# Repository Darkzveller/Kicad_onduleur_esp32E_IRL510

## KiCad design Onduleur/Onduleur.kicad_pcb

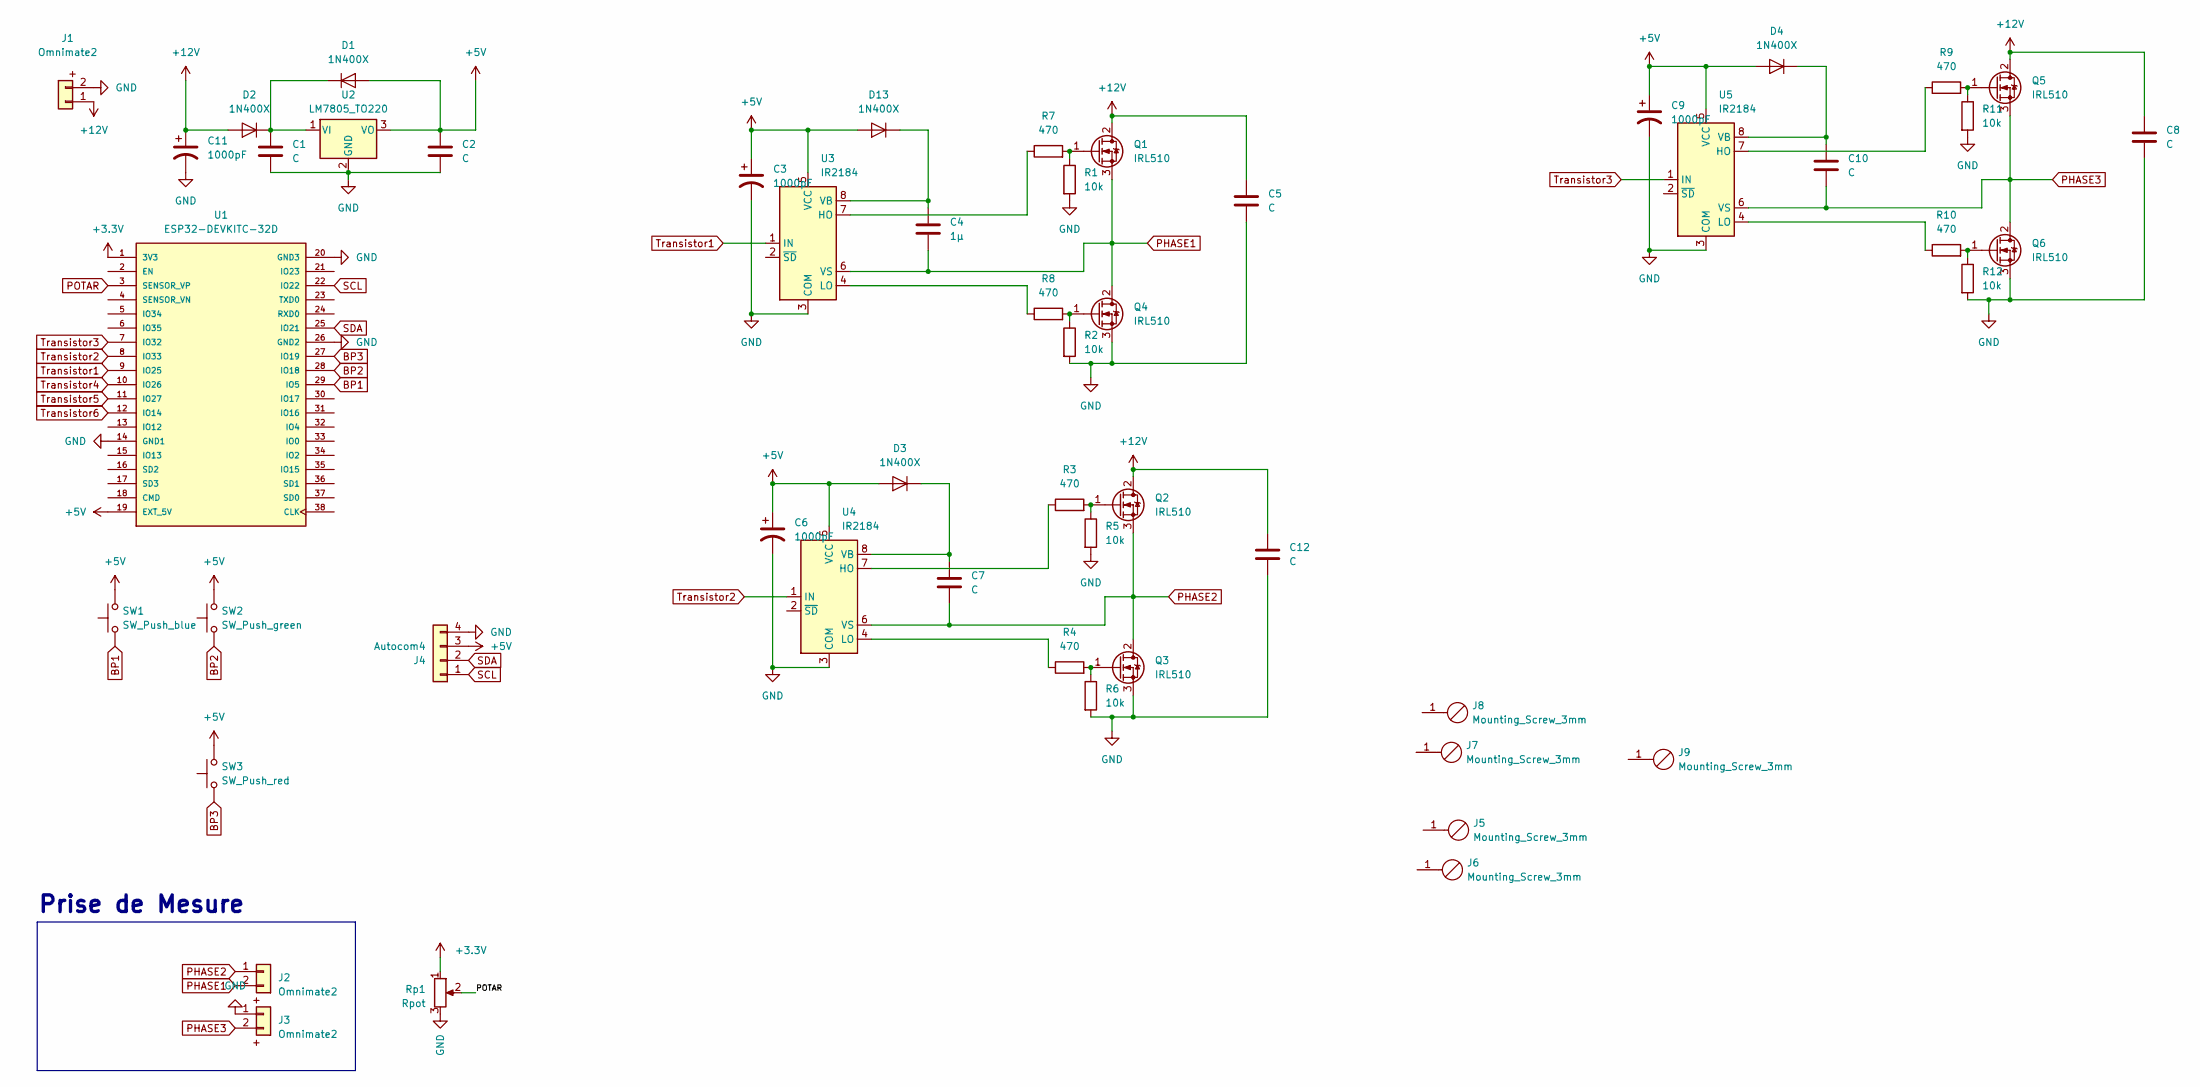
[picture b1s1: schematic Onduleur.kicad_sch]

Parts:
C1, C2, C7, C10: C; C_Rect_L7.0mm_W2.5mm_P5.00mm
C3, C6, C9: 1000pF; CP_Radial_D5.0mm_P2.50mm
C4: 1µ; C_Rect_L7.0mm_W2.5mm_P5.00mm
C5, C8, C12: C; C_Rect_L19.0mm_W5.0mm_P15.00mm
C11: 1000pF; CP_Radial_D10.0mm_P5.00mm
D1, D2, D3, D4, D13: 1N400X; D_DO-41_SOD81_P10.16mm_Horizontal
J1, J2, J3: Omnimate2; OmnimateSL-5,08_1x02_P5.08mm_Vertical
J4: Autocom4; PinHeader_1x04_P2.00mm_Vertical
J5, J6, J7, J8, J9: Mounting_Screw_3mm
Q1, Q2, Q3, Q4, Q5, Q6: IRL510; TO-220-3_Horizontal_TabDown
R1, R2, R5, R6, R11, R12: 10k; R_Axial_DIN0207_L6.3mm_D2.5mm_P10.16mm_Horizontal
R3, R4, R7, R8, R9, R10: 470; R_Axial_DIN0207_L6.3mm_D2.5mm_P10.16mm_Horizontal
Rp1: Rpot; Potentiometer_ACP_CA9-H5_Horizontal
SW1: SW_Push_blue; SW_PUSH_5mm_blue
SW2: SW_Push_green; SW_PUSH_5mm_green
SW3: SW_Push_red; SW_PUSH_5mm_red
U1: ESP32-DEVKITC-32D; MODULE_ESP32-DEVKITC-32D; PARTREV 4
U2: LM7805_TO220; TO-220-3_Horizontal_TabDown
U3, U4, U5: IR2184; DIP-8_W7.62mm_LongPads

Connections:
+3.3V: Rp1.1, U1.1 (3V3)
+5V: C2.1, C3.1, C6.1, C9.1, D1.2 (A), D3.2 (A), D4.2 (A), D13.2 (A), J4.3, SW1.2, SW2.2, SW3.2, U1.19 (EXT_5V), U2.3 (VO), U3.5 (VCC), U4.5 (VCC), U5.5 (VCC)
+12V: C5.1, C8.1, C11.1, C12.1, D2.2 (A), J1.1, Q1.2 (D), Q2.2 (D), Q5.2 (D)
BP1: SW1.1, U1.29 (IO5)
BP2: SW2.1, U1.28 (IO18)
BP3: SW3.1, U1.27 (IO19)
GND: C1.2, C2.2, C3.2, C5.2, C6.2, C8.2, C9.2, C11.2, C12.2, J1.2, J3.1, J4.4, Q3.3 (S), Q4.3 (S), Q6.3 (S), R1.2, R2.2, R5.2, R6.2, R11.2, R12.2, Rp1.3, U1.14 (GND1), U1.20 (GND3), U1.26 (GND2), U2.2 (GND), U3.3 (COM), U4.3 (COM), U5.3 (COM)
unnamed: C1.1, D1.1 (K), D2.1 (K), U2.1 (VI)
unnamed: C7.1, D3.1 (K), U4.8 (VB)
unnamed: C10.1, D4.1 (K), U5.8 (VB)
unnamed: C4.1, D13.1 (K), U3.8 (VB)
unnamed: Q1.1 (G), R1.1, R7.2
unnamed: Q2.1 (G), R3.2, R5.1
unnamed: Q3.1 (G), R4.2, R6.1
unnamed: Q4.1 (G), R2.1, R8.2
unnamed: Q5.1 (G), R9.2, R11.1
unnamed: Q6.1 (G), R10.2, R12.1
unnamed: R7.1, U3.7 (HO)
unnamed: R8.1, U3.4 (LO)
unnamed: R3.1, U4.7 (HO)
unnamed: R4.1, U4.4 (LO)
unnamed: R9.1, U5.7 (HO)
unnamed: R10.1, U5.4 (LO)
PHASE1: C4.2, J2.2, Q1.3 (S), Q4.2 (D), U3.6 (VS)
PHASE2: C7.2, J2.1, Q2.3 (S), Q3.2 (D), U4.6 (VS)
PHASE3: C10.2, J3.2, Q5.3 (S), Q6.2 (D), U5.6 (VS)
POTAR: Rp1.2, U1.3 (SENSOR_VP)
SCL: J4.1, U1.22 (IO22)
SDA: J4.2, U1.25 (IO21)
Transistor1: U1.9 (IO25), U3.1 (IN)
Transistor2: U1.8 (IO33), U4.1 (IN)
Transistor3: U1.7 (IO32), U5.1 (IN)
Transistor4: U1.10 (IO26)
Transistor5: U1.11 (IO27)
Transistor6: U1.12 (IO14)

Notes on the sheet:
Prise de Mesure

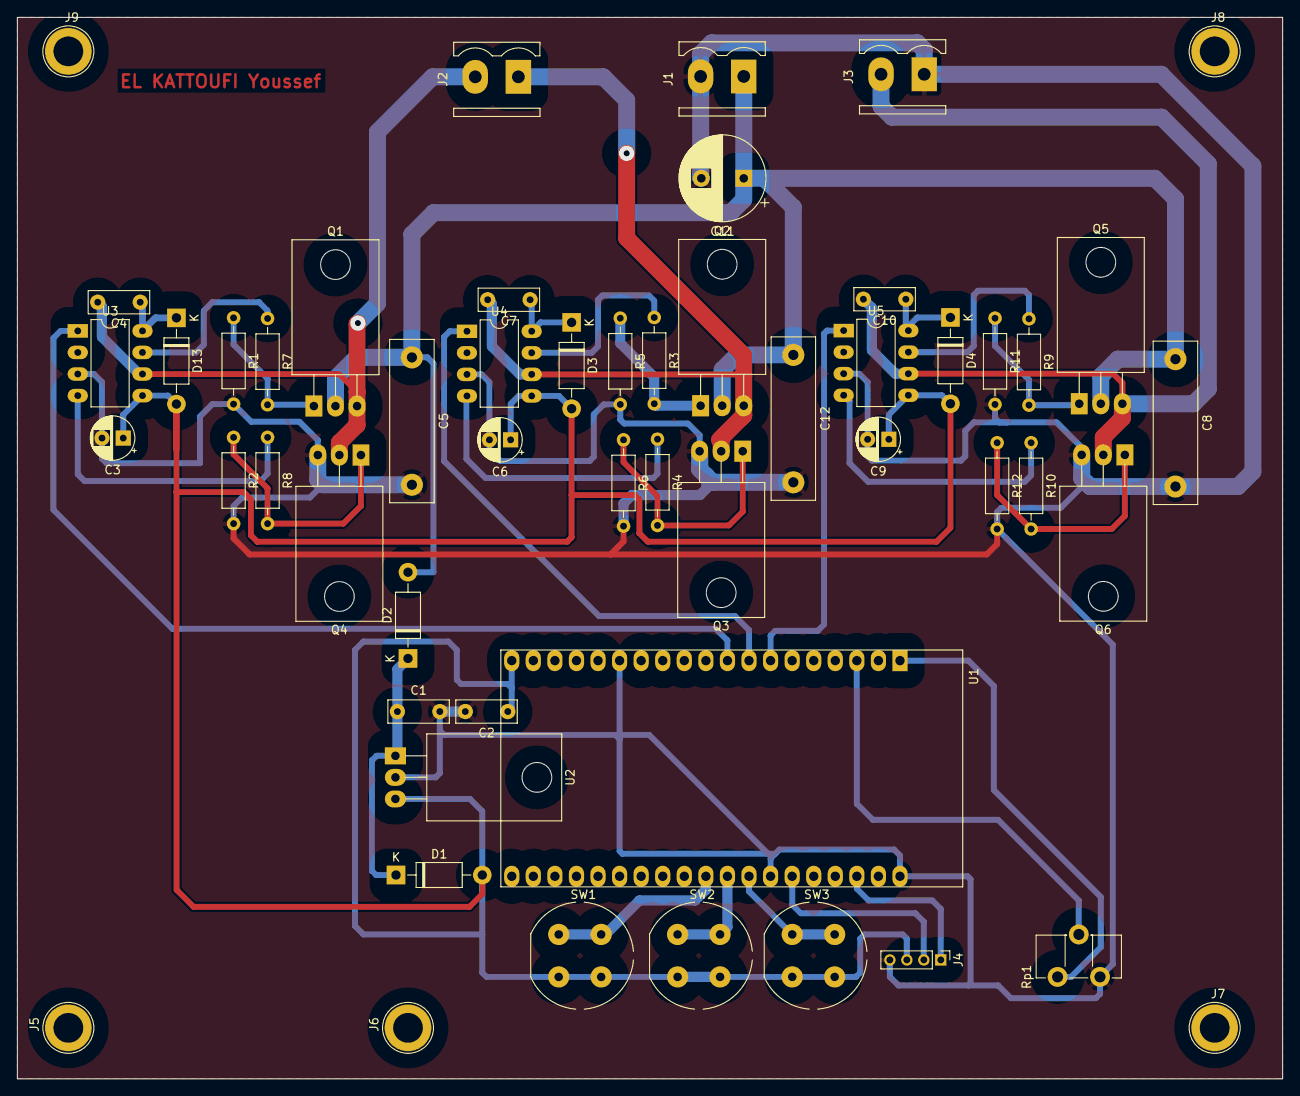
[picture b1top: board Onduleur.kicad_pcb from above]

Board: 2 copper layers, 149.0 x 125.0 mm, 53 parts (0 on the bottom side), 32 nets.

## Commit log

2025-06-23 Erreur de ma part, véritable first commit
